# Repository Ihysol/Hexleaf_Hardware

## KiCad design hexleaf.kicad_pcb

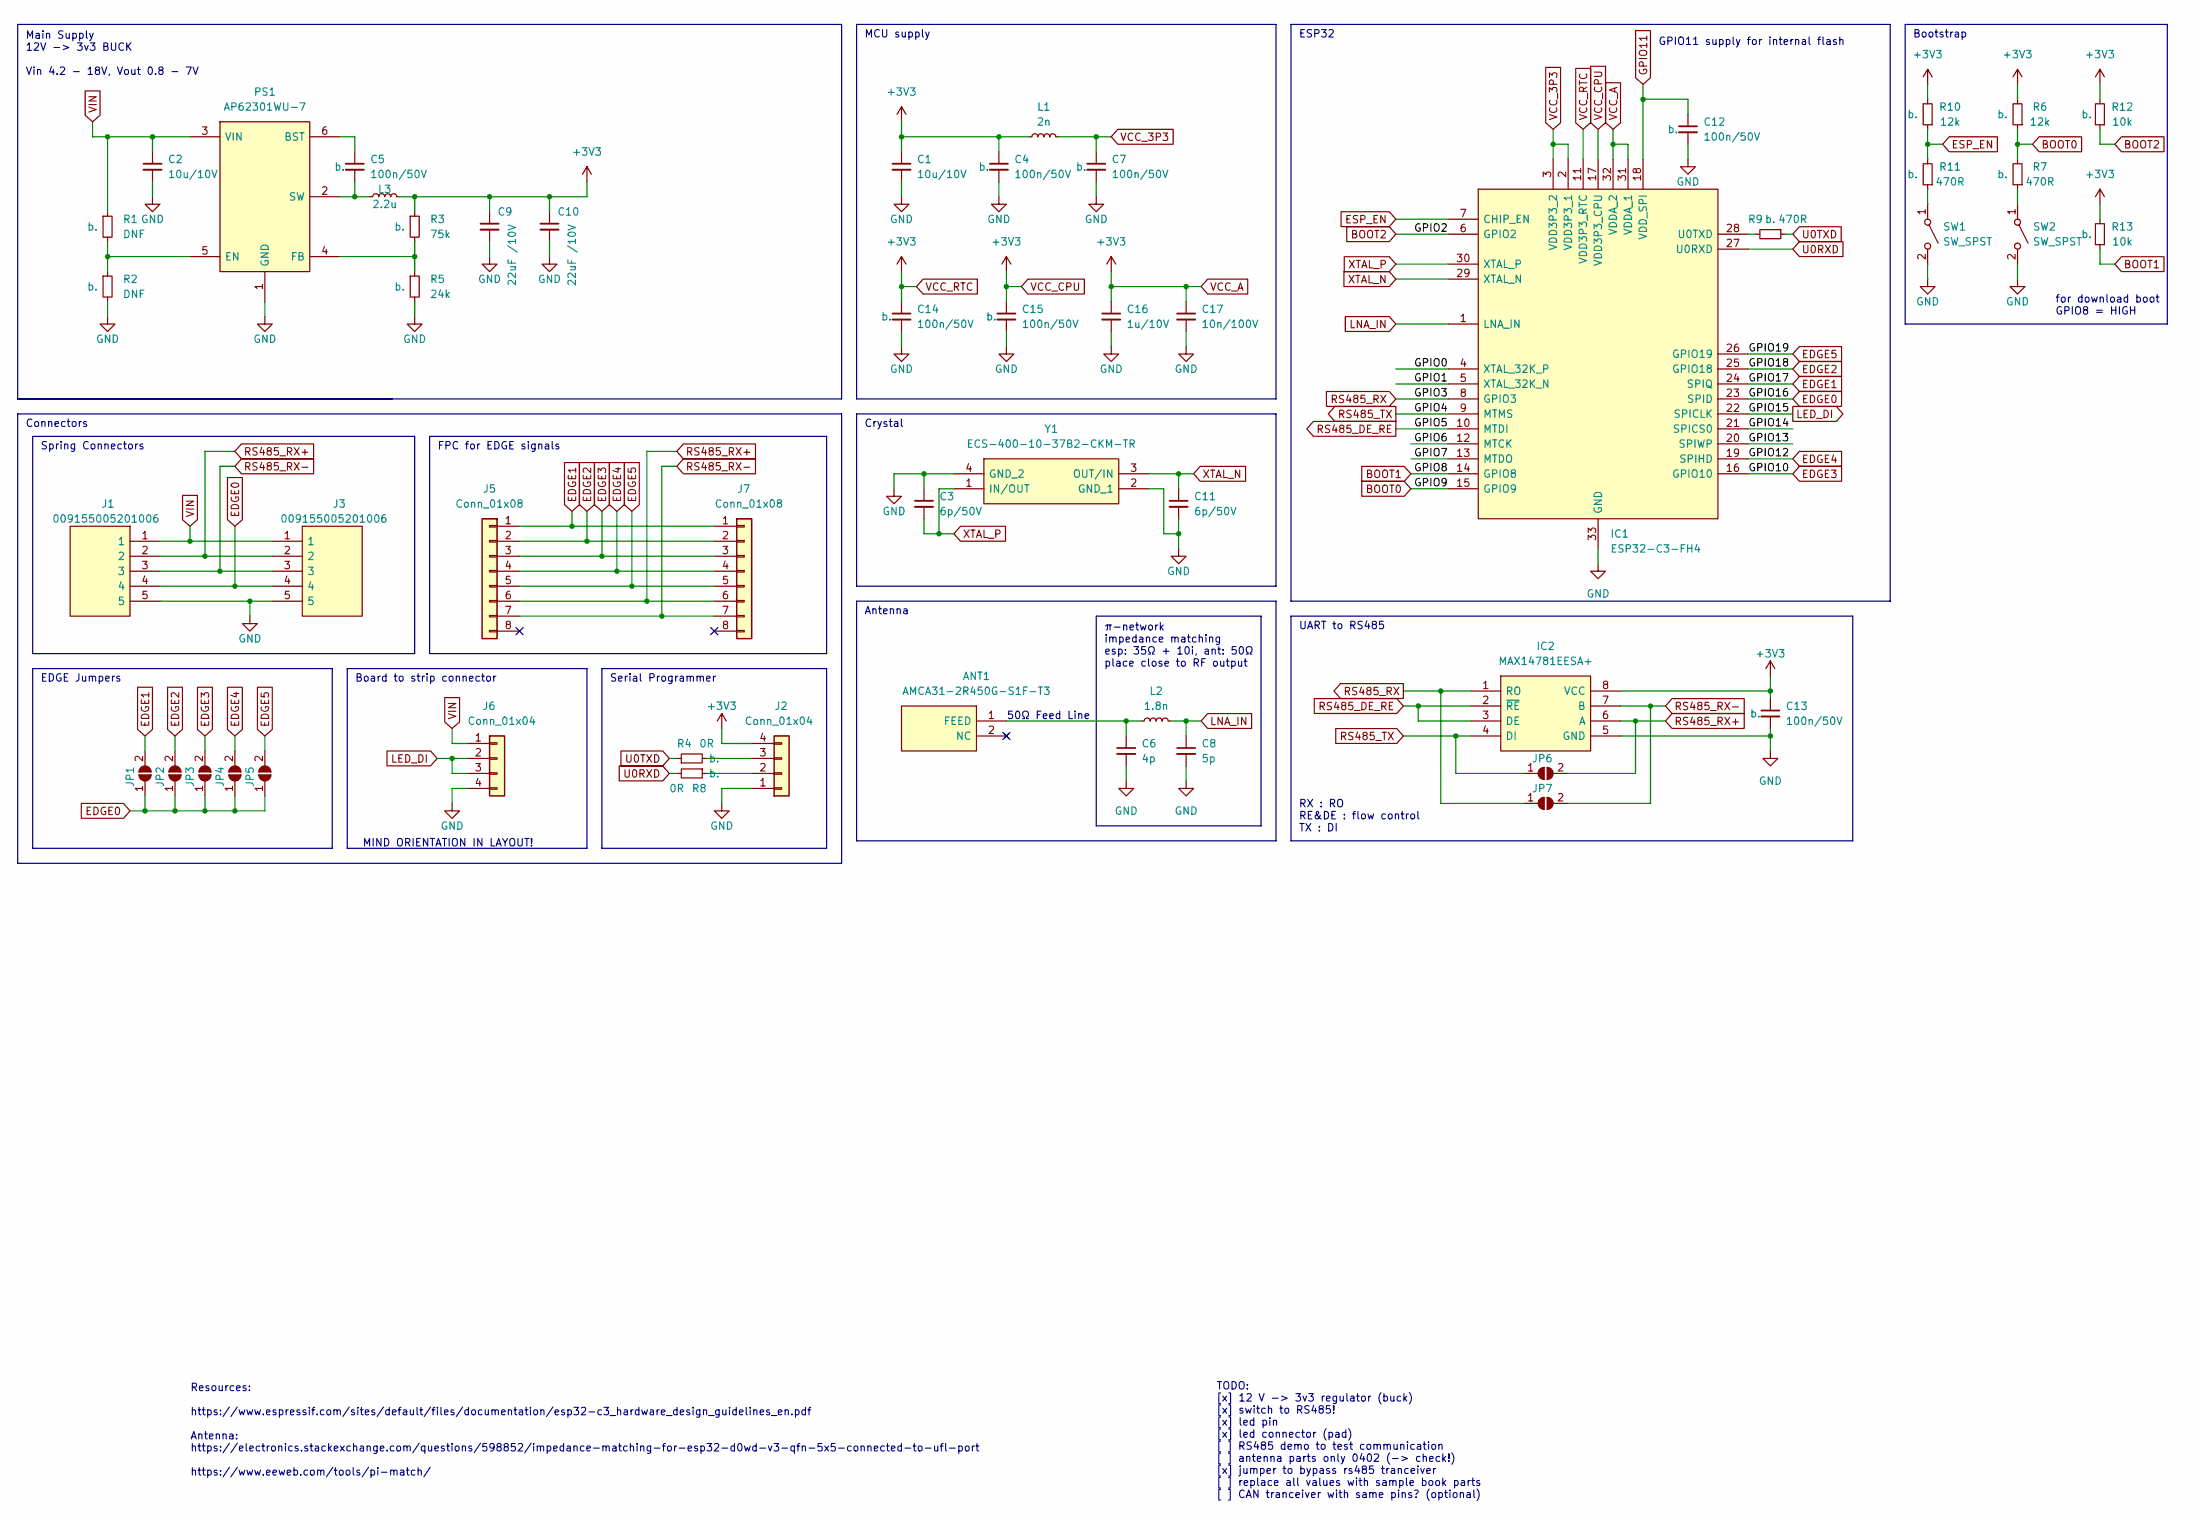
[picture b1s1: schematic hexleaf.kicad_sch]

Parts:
ANT1: AMCA31-2R450G-S1F-T3; ANTC3216X140N; Mouser Part Number 815-CA312R450GS1FT3
C1, C2: 10u/10V; R_0805_2012Metric
C3, C11: 6p/50V; C_0402_1005Metric
C4, C5, C7, C12, C13, C14, C15: 100n/50V; R_0603_1608Metric
C6: 4p; C_0402_1005Metric
C8: 5p; C_0402_1005Metric
C9, C10: 22uF /10V; C_0603_1608Metric; Mouser Part Number 187-CL10A226MP8NUNE
C16: 1u/10V; R_0603_1608Metric
C17: 10n/100V; R_0805_2012Metric
IC1: ESP32-C3-FH4; QFN50P500X500X90-33N-D; Mouser Part Number 356-ESP32-C3FH4
IC2: MAX14781EESA+; SOIC127P600X175-8N; Mouser Part Number 700-MAX14781EESA+
J1, J3: 009155005201006; Mouser Part Number 581-009155005201006
J2: Conn_01x04; PinHeader_1x04_P2.54mm_Vertical
J5, J7: Conn_01x08
J6: Conn_01x04; WS2815_Strip_4P_Full
JP1, JP2, JP3, JP4, JP5, JP6, JP7: SolderJumper_2_Open; SolderJumper-2_P1.3mm_Open_TrianglePad1.0x1.5mm
L1: 2n; C_0402_1005Metric
L2: 1.8n; L_0402_1005Metric
L3: 2.2u; L_5024
PS1: AP62301WU-7; SOT95P280X100-6N; Mouser Part Number 621-AP62301WU-7
R1, R2: DNF; R_0402_1005Metric
R3: 75k; R_0402_1005Metric
R4, R8: 0R; R_0402_1005Metric
R5: 24k; R_0402_1005Metric
R6, R10: 12k; R_0402_1005Metric
R7, R9, R11: 470R; R_0402_1005Metric
R12, R13: 10k; R_0402_1005Metric
SW1, SW2: SW_SPST; KXT3-1831561
Y1: ECS-400-10-37B2-CKM-TR; ECS4001037B2CKMTR; Mouser Part Number 520-400-10-37B2CKMTR

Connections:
/GPIO0: IC1.4 (XTAL_32K_P)
/GPIO1: IC1.5 (XTAL_32K_N)
/GPIO6: IC1.12 (MTCK)
/GPIO7: IC1.13 (MTDO)
/GPIO13: IC1.20 (SPIWP)
/GPIO14: IC1.21 (SPICS0)
BOOT0: IC1.15 (GPIO9), R6.1, R7.2
BOOT1: IC1.14 (GPIO8), R13.1
BOOT2: IC1.6 (GPIO2), R12.1
EDGE0: IC1.23 (SPID), J1.4, J3.4, JP1.1 (A), JP2.1 (A), JP3.1 (A), JP4.1 (A), JP5.1 (A)
EDGE1: IC1.24 (SPIQ), J5.1, J7.1, JP1.2 (B)
EDGE2: IC1.25 (GPIO18), J5.2, J7.2, JP2.2 (B)
EDGE3: IC1.16 (GPIO10), J5.3, J7.3, JP3.2 (B)
EDGE4: IC1.19 (SPIHD), J5.4, J7.4, JP4.2 (B)
EDGE5: IC1.26 (GPIO19), J5.5, J7.5, JP5.2 (B)
ESP_EN: IC1.7 (CHIP_EN), R10.1, R11.2
GND: C1.2, C2.2, C3.1, C4.2, C6.2, C7.2, C8.2, C9.2, C10.2, C11.2, C12.2, C13.2, C14.2, C15.2, C16.2, C17.2, IC1.33 (GND), IC2.5 (GND), J1.5, J2.1, J3.5, J6.4, PS1.1 (GND), R2.2, R5.2, SW1.2 (B), SW2.2 (B), Y1.2 (GND_1), Y1.4 (GND_2)
GPIO11: C12.1, IC1.18 (VDD_SPI)
LED_DI: IC1.22 (SPICLK), J6.2, J6.3
LNA_IN: C8.1, IC1.1 (LNA_IN), L2.2
unnamed: ANT1.1 (FEED), C6.1, L2.1
unnamed: C5.1, PS1.6 (BST)
unnamed: C5.2, L3.1, PS1.2 (SW)
unnamed: IC1.28 (U0TXD), R9.2
unnamed: J2.2, R8.1
unnamed: J2.3, R4.2
unnamed: PS1.4 (FB), R3.2, R5.1
unnamed: PS1.5 (EN), R1.2, R2.1
unnamed: R7.1, SW2.1 (A)
unnamed: R11.1, SW1.1 (A)
RS485_DE_RE: IC1.10 (MTDI), IC2.2 (~RE), IC2.3 (DE)
RS485_RX: IC1.8 (GPIO3), IC2.1 (RO), JP7.1 (A)
RS485_RX+: IC2.6 (A), J1.2, J3.2, J5.6, J7.6, JP6.2 (B)
RS485_RX-: IC2.7 (B), J1.3, J3.3, J5.7, J7.7, JP7.2 (B)
RS485_TX: IC1.9 (MTMS), IC2.4 (DI), JP6.1 (A)
U0RXD: IC1.27 (U0RXD), R8.2
U0TXD: R4.1, R9.1
VCC_3P3: C7.1, IC1.2 (VDD3P3_1), IC1.3 (VDD3P3_2), L1.2
VCC_A: C1.1, C4.1, C9.1, C10.1, C13.1, C14.1, C15.1, C16.1, C17.1, IC1.11 (VDD3P3_RTC), IC1.17 (VDD3P3_CPU), IC1.31 (VDDA_1), IC1.32 (VDDA_2), IC2.8 (VCC), J2.4, L1.1, L3.2, R3.1, R6.2, R10.2, R12.2, R13.2
VIN: C2.1, J1.1, J3.1, J6.1, PS1.3 (VIN), R1.1
XTAL_N: C11.1, IC1.29 (XTAL_N), Y1.3 (OUT/IN)
XTAL_P: C3.2, IC1.30 (XTAL_P), Y1.1 (IN/OUT)

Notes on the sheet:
Connectors
π-network impedance matching esp: 35Ω + 10i, ant: 50Ω place close to RF output
Spring Connectors
RX : RO RE&DE : flow control TX : DI
Main Supply 12V -> 3v3 BUCK Vin 4.2 - 18V, Vout 0.8 - 7V
FPC for EDGE signals
MIND ORIENTATION IN LAYOUT!
GPIO11 supply for internal flash
Serial Programmer
Board to strip connector
for download boot GPIO8 = HIGH
MCU supply
EDGE Jumpers
Antenna
ESP32
Resources: https://www.espressif.com/sites/default/files/documentation/esp32-c3_hardware_design_guidelines_en.pdf Antenna: https://electronics.stackexchange.com/questions/598852/impedance-matching-for-esp32-d0wd-v3-qfn-5x5-connected-to-ufl-port https://www.eeweb.com/tools/pi-match/
UART to RS485
Crystal
Bootstrap
50Ω Feed Line
TODO: [x] 12 V -> 3v3 regulator (buck) [x] switch to RS485! [x] led pin [x] led connector (pad) [ ] RS485 demo to test communication [ ] antenna parts only 0402 (-> check!) [x] jumper to bypass rs485 tranceiver [ ] replace all values with sample book parts [ ] CAN tranceiver with same pins? (option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

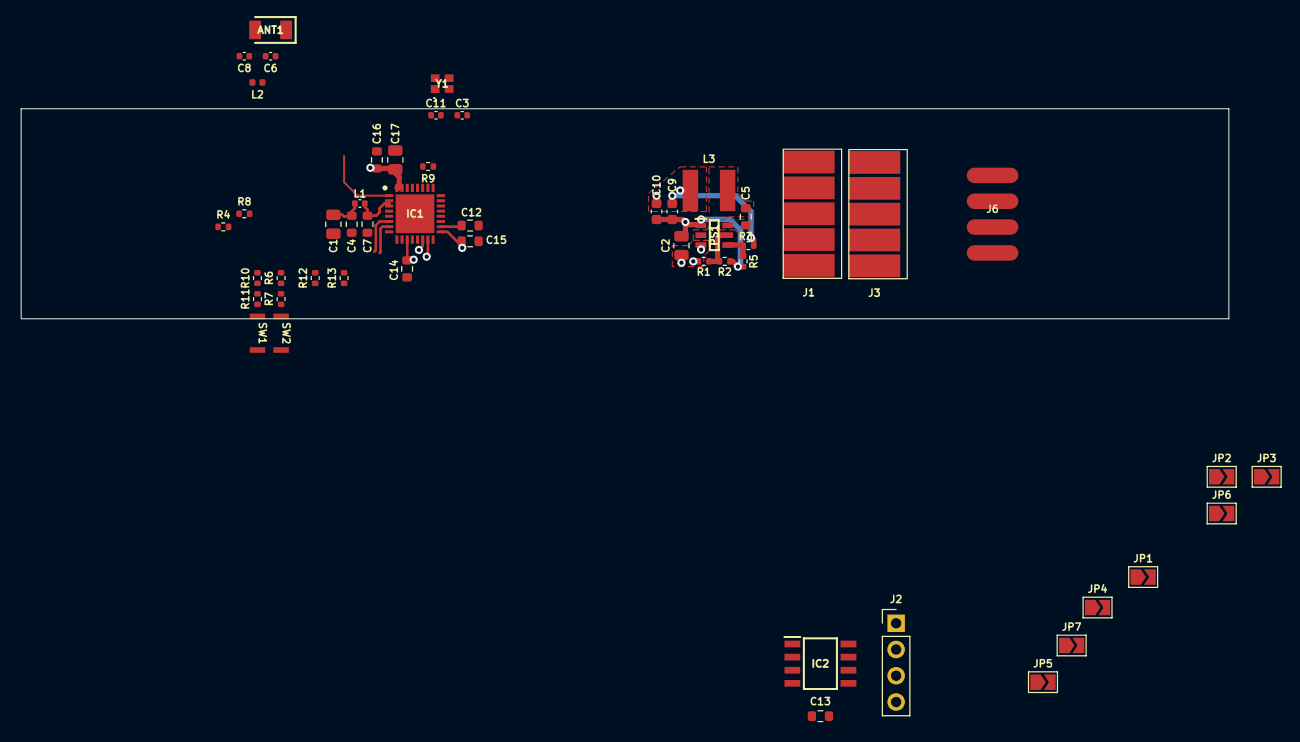
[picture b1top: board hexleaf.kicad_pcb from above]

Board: 4 copper layers, 116.8 x 20.3 mm, 51 parts (0 on the bottom side), 36 nets.

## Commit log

2022-05-07 added TODO
2022-05-07 added spring connector libs
2022-05-07 added spring connectors & started setup for edge-system
2022-05-08 antenna parts
2022-05-08 updated todo
2022-05-09 added connectors
2022-05-10 added 5 pin connector
2022-05-11 moved EDGE signal from GPIO8(strapping pin)
2022-05-11 added strapping pin
2022-05-12 uart1 planning
2022-05-21 redone gpio0 labels + added rs485 pins
2022-05-21 led pins and RS485 bypass jumper
2022-05-21 added buck
2022-05-21 changed parts and ordered first batch for prototyping
2022-05-21 added alternative to RS485 ic
2022-05-22 started layout
2022-08-03 updated schematic (crystal symbol)
